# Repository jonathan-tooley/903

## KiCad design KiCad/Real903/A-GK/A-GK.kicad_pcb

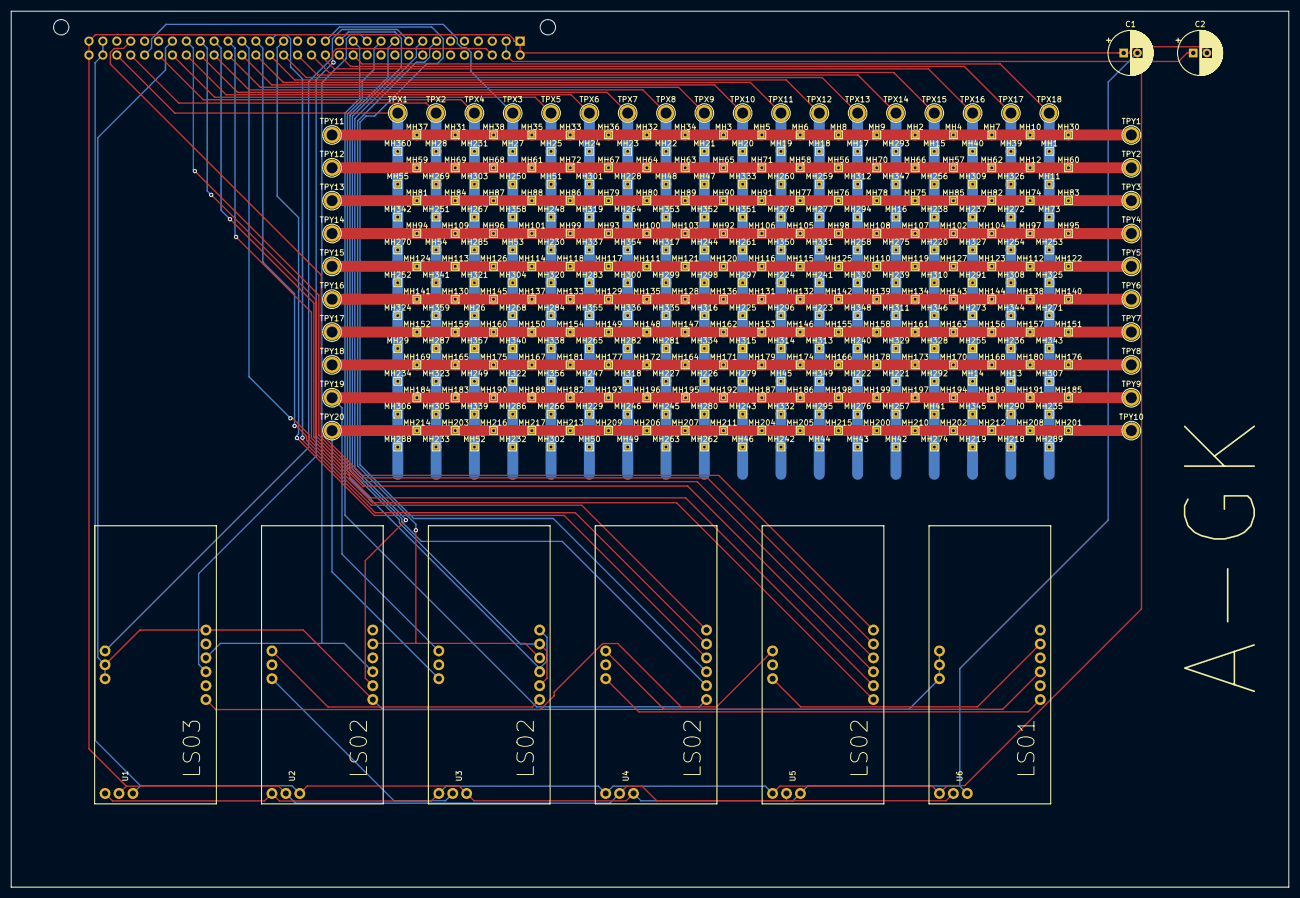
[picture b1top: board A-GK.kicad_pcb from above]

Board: 2 copper layers, 233.3 x 160.0 mm, 407 parts (1 on the bottom side), 57 nets.

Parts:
C1, C2: 6u8; CP_Radial_D8.0mm_P2.50mm
J1: J1; DIN41612_B_2x32_Horizontal
MH1, MH2, MH3, MH4, MH5, MH6, MH7, MH8, MH9, MH10, MH11, MH12, MH13, MH14, MH15, MH16, MH17, MH18, MH19, MH20, MH21, MH22, MH23, MH24, MH25, MH26, MH27, MH28, MH29, MH30, MH31, MH32, MH33, MH34, MH35, MH36, MH37, MH38, MH39, MH40, MH41, MH42, MH43, MH44, MH45, MH46, MH47, MH48, MH49, MH50, MH51, MH52, MH53, MH54, MH55, MH56, MH57, MH58, MH59, MH60, MH61, MH62, MH63, MH64, MH65, MH66, MH67, MH68, MH69, MH70, MH71, MH72, MH73, MH74, MH75, MH76, MH77, MH78, MH79, MH80, MH81, MH82, MH83, MH84, MH85, MH86, MH87, MH88, MH89, MH90, MH91, MH92, MH93, MH94, MH95, MH96, MH97, MH98, MH99, MH100, MH101, MH102, MH103, MH104, MH105, MH106, MH107, MH108, MH109, MH110, MH111, MH112, MH113, MH114, MH115, MH116, MH117, MH118, MH119, MH120, MH121, MH122, MH123, MH124, MH125, MH126, MH127, MH128, MH129, MH130, MH131, MH132, MH133, MH134, MH135, MH136, MH137, MH138, MH139, MH140, MH141, MH142, MH143, MH144, MH145, MH146, MH147, MH148, MH149, MH150, MH151, MH152, MH153, MH154, MH155, MH156, MH157, MH158, MH159, MH160, MH161, MH162, MH163, MH164, MH165, MH166, MH167, MH168, MH169, MH170, MH171, MH172, MH173, MH174, MH175, MH176, MH177, MH178, MH179, MH180, MH181, MH182, MH183, MH184, MH185, MH186, MH187, MH188, MH189, MH190, MH191, MH192, MH193, MH194, MH195, MH196, MH197, MH198, MH199, MH200, MH201, MH202, MH203, MH204, MH205, MH206, MH207, MH208, MH209, MH210, MH211, MH212, MH213, MH214, MH215, MH216, MH217, MH218, MH219, MH220, MH221, MH222, MH223, MH224, MH225, MH226, MH227, MH228, MH229, MH230, MH231, MH232, MH233, MH234, MH235, MH236, MH237, MH238, MH239, MH240, MH241, MH242, MH243, MH244, MH245, MH246, MH247, MH248, MH249, MH250, MH251, MH252, MH253, MH254, MH255, MH256, MH257, MH258, MH259, MH260, MH261, MH262, MH263, MH264, MH265, MH266, MH267, MH268, MH269, MH270, MH271, MH272, MH273, MH274, MH275, MH276, MH277, MH278, MH279, MH280, MH281, MH282, MH283, MH284, MH285, MH286, MH287, MH288, MH289, MH290, MH291, MH292, MH293, MH294, MH295, MH296, MH297, MH298, MH299, MH300, MH301, MH302, MH303, MH304, MH305, MH306, MH307, MH308, MH309, MH310, MH311, MH312, MH313, MH314, MH315, MH316, MH317, MH318, MH319, MH320, MH321, MH322, MH323, MH324, MH325, MH326, MH327, MH328, MH329, MH330, MH331, MH332, MH333, MH334, MH335, MH336, MH337, MH338, MH339, MH340, MH341, MH342, MH343, MH344, MH345, MH346, MH347, MH348, MH349, MH350, MH351, MH352, MH353, MH354, MH355, MH356, MH357, MH358, MH359, MH360: TestPoint_THTPad_1.0x1.0mm_Drill0.5mm
TPX1, TPX2, TPX3, TPX4, TPX5, TPX6, TPX7, TPX8, TPX9, TPX10, TPX11, TPX12, TPX13, TPX14, TPX15, TPX16, TPX17, TPX18: TestPoint_Plated_Hole_D2.0mm
TPY1, TPY2, TPY3, TPY4, TPY5, TPY6, TPY7, TPY8, TPY9, TPY10, TPY11, TPY12, TPY13, TPY14, TPY15, TPY16, TPY17, TPY18, TPY19, TPY20: TestPoint_Plated_Hole_D2.0mm
U1: LS03; LSA
U2, U3, U4, U5: LS02; LSA
U6: LS01; LSA

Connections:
2: MH200.1, MH201.1, MH202.1, MH203.1, MH204.1, MH205.1, MH206.1, MH207.1, MH208.1, MH209.1, MH210.1, MH211.1, MH212.1, MH213.1, MH214.1, MH215.1, MH216.1, MH217.1, TPY10.1, TPY20.1, U3.11
4: MH182.1, MH183.1, MH184.1, MH185.1, MH186.1, MH187.1, MH188.1, MH189.1, MH190.1, MH191.1, MH192.1, MH193.1, MH194.1, MH195.1, MH196.1, MH197.1, MH198.1, MH199.1, TPY9.1, TPY19.1, U3.13
6v: C2.1, J1.2, J1.B, U1.21, U2.21, U3.21, U4.21, U5.21, U6.21
GND: C1.1, C2.2, J1.1, J1.32, J1.A, J1.AL, U1.22, U2.22, U4.22, U5.22, U6.22
II1m: J1.P, MH1.1, MH11.1, MH73.1, MH235.1, MH253.1, MH271.1, MH289.1, MH307.1, MH325.1, MH343.1, TPX18.1
II2m: J1.R, MH13.1, MH39.1, MH218.1, MH236.1, MH254.1, MH272.1, MH290.1, MH308.1, MH326.1, MH344.1, TPX17.1
II3m: J1.S, MH14.1, MH40.1, MH219.1, MH237.1, MH255.1, MH273.1, MH291.1, MH309.1, MH327.1, MH345.1, TPX16.1
II4m: J1.T, MH15.1, MH41.1, MH220.1, MH238.1, MH256.1, MH274.1, MH292.1, MH310.1, MH328.1, MH346.1, TPX15.1
II5m: J1.U, MH16.1, MH42.1, MH221.1, MH239.1, MH257.1, MH275.1, MH293.1, MH311.1, MH329.1, MH347.1, TPX14.1
II6m: J1.V, MH17.1, MH43.1, MH222.1, MH240.1, MH258.1, MH276.1, MH294.1, MH312.1, MH330.1, MH348.1, TPX13.1
II7m: J1.W, MH18.1, MH44.1, MH223.1, MH241.1, MH259.1, MH277.1, MH295.1, MH313.1, MH331.1, MH349.1, TPX12.1
II8m: J1.X, MH19.1, MH45.1, MH224.1, MH242.1, MH260.1, MH278.1, MH296.1, MH314.1, MH332.1, MH350.1, TPX11.1
II9m: J1.Y, MH20.1, MH46.1, MH225.1, MH243.1, MH261.1, MH279.1, MH297.1, MH315.1, MH333.1, MH351.1, TPX10.1
II10m: J1.Z, MH21.1, MH47.1, MH226.1, MH244.1, MH262.1, MH280.1, MH298.1, MH316.1, MH334.1, MH352.1, TPX9.1
II11m: J1.AA, MH22.1, MH48.1, MH227.1, MH245.1, MH263.1, MH281.1, MH299.1, MH317.1, MH335.1, MH353.1, TPX8.1
II12m: J1.AB, MH23.1, MH49.1, MH228.1, MH246.1, MH264.1, MH282.1, MH300.1, MH318.1, MH336.1, MH354.1, TPX7.1
II13m: J1.AC, MH24.1, MH50.1, MH229.1, MH247.1, MH265.1, MH283.1, MH301.1, MH319.1, MH337.1, MH355.1, TPX6.1
II14m: J1.AD, MH25.1, MH51.1, MH230.1, MH248.1, MH266.1, MH284.1, MH302.1, MH320.1, MH338.1, MH356.1, TPX5.1
II15m: J1.AE, MH26.1, MH52.1, MH231.1, MH249.1, MH267.1, MH285.1, MH303.1, MH321.1, MH339.1, MH357.1, TPX4.1
II16m: J1.AF, MH27.1, MH53.1, MH232.1, MH250.1, MH268.1, MH286.1, MH304.1, MH322.1, MH340.1, MH358.1, TPX3.1
II17m: J1.AH, MH28.1, MH54.1, MH233.1, MH251.1, MH269.1, MH287.1, MH305.1, MH323.1, MH341.1, MH359.1, TPX2.1
II18m: J1.AJ, MH29.1, MH55.1, MH234.1, MH252.1, MH270.1, MH288.1, MH306.1, MH324.1, MH342.1, MH360.1, TPX1.1
IIG: J1.26, U1.6, U1.11, U1.12, U2.1, U6.11, U6.12, U6.13
IIG-: J1.9, U1.13
IIS: J1.8, U2.2
J1': J1.7, U2.5, U3.4
J2-': J1.10, U3.2, U3.5
J3': J1.11, U3.3, U3.6
J3-': J1.C, U1.3
J4-: J1.12, U1.4, U2.3
J5: J1.13, U4.1
J6: J1.14, U4.2
J7: J1.15, U4.3
J8: J1.18, U4.4
J9: J1.19, U4.5
J10: J1.20, U4.6
J11: J1.21, U5.1
J12: J1.22, U5.2
J13: J1.23, U5.3
J14-: J1.24, U5.4
J15-: J1.25, U5.5
J16-: J1.29, U5.6
Neg6v: C1.2, J1.31, J1.AK, U1.23, U2.23, U3.23, U4.23, U5.23, U6.23
unnamed: MH2.1, MH3.1, MH4.1, MH5.1, MH6.1, MH7.1, MH8.1, MH9.1, MH10.1, MH30.1, MH31.1, MH32.1, MH33.1, MH34.1, MH35.1, MH36.1, MH37.1, MH38.1, TPY1.1, TPY11.1
unnamed: MH12.1, MH56.1, MH57.1, MH58.1, MH59.1, MH60.1, MH61.1, MH62.1, MH63.1, MH64.1, MH65.1, MH66.1, MH67.1, MH68.1, MH69.1, MH70.1, MH71.1, MH72.1, TPY2.1, TPY12.1
unnamed: MH74.1, MH75.1, MH76.1, MH77.1, MH78.1, MH79.1, MH80.1, MH81.1, MH82.1, MH83.1, MH84.1, MH85.1, MH86.1, MH87.1, MH88.1, MH89.1, MH90.1, MH91.1, TPY3.1, TPY13.1
unnamed: MH92.1, MH93.1, MH94.1, MH95.1, MH96.1, MH97.1, MH98.1, MH99.1, MH100.1, MH101.1, MH102.1, MH103.1, MH104.1, MH105.1, MH106.1, MH107.1, MH108.1, MH109.1, TPY4.1, TPY14.1
unnamed: MH110.1, MH111.1, MH112.1, MH113.1, MH114.1, MH115.1, MH116.1, MH117.1, MH118.1, MH119.1, MH120.1, MH121.1, MH122.1, MH123.1, MH124.1, MH125.1, MH126.1, MH127.1, TPY5.1, TPY15.1
unnamed: MH128.1, MH129.1, MH130.1, MH131.1, MH132.1, MH133.1, MH134.1, MH135.1, MH136.1, MH137.1, MH138.1, MH139.1, MH140.1, MH141.1, MH142.1, MH143.1, MH144.1, MH145.1, TPY6.1, TPY16.1
unnamed: MH146.1, MH147.1, MH148.1, MH149.1, MH150.1, MH151.1, MH152.1, MH153.1, MH154.1, MH155.1, MH156.1, MH157.1, MH158.1, MH159.1, MH160.1, MH161.1, MH162.1, MH163.1, TPY7.1, TPY17.1
unnamed: MH164.1, MH165.1, MH166.1, MH167.1, MH168.1, MH169.1, MH170.1, MH171.1, MH172.1, MH173.1, MH174.1, MH175.1, MH176.1, MH177.1, MH178.1, MH179.1, MH180.1, MH181.1, TPY8.1, TPY18.1
unnamed: U1.1, U5.13
unnamed: U2.13, U3.1
unnamed: U4.11, U6.1
unnamed: U4.13, U6.3
unnamed: U5.11, U6.5
U3GND: U2.11, U3.22

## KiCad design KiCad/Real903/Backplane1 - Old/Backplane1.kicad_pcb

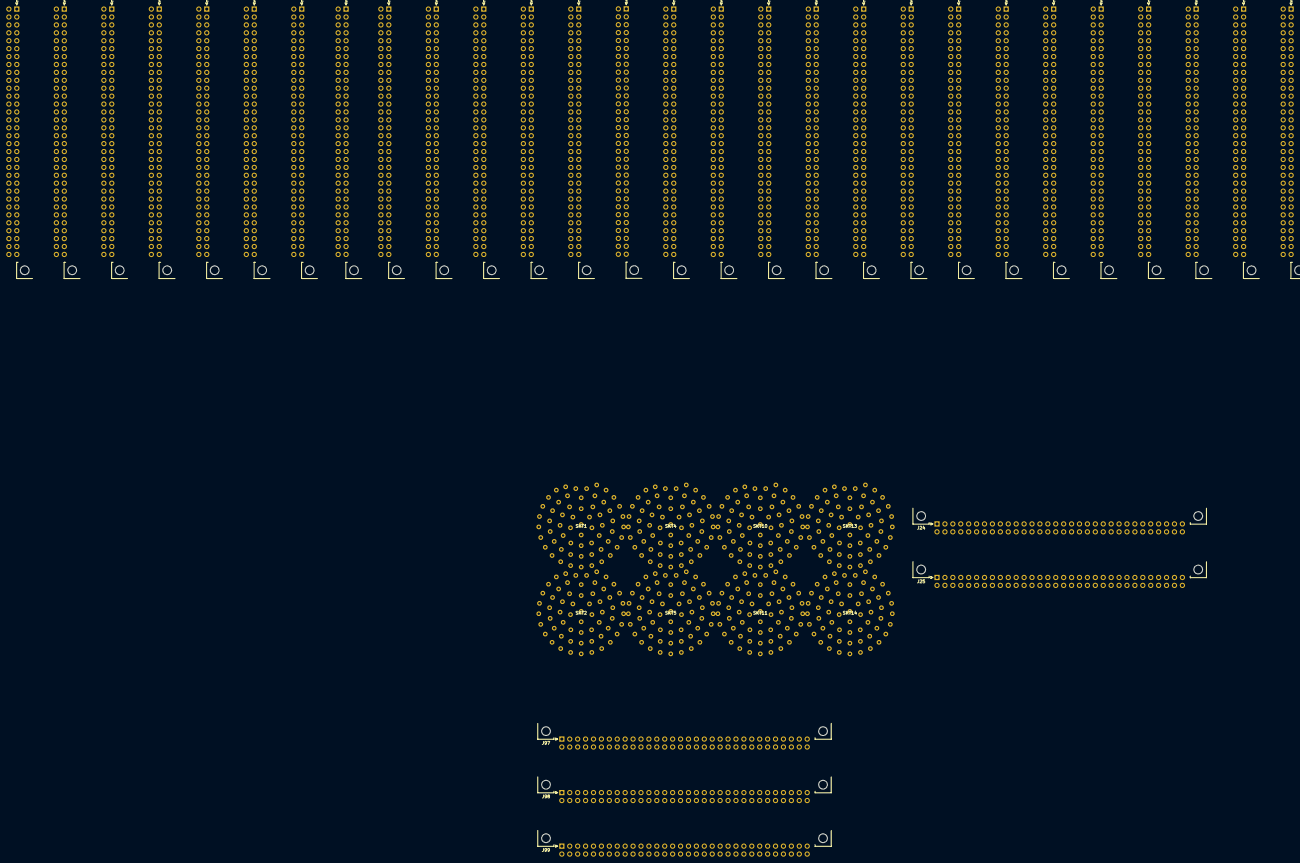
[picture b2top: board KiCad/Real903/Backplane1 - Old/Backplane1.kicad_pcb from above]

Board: 8 copper layers, 41 parts (0 on the bottom side), 564 nets, no tracks yet.

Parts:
J24, J25, J28, J29, J30, J31, J32, J34, J35, J36, J37, J38, J39, J40, J41, J42, J43, J44, J45, J46, J47, J48, J49, J50, J51, J52, J53, J54, J55, J56, J97, J98, J99: Conn_02x32; DIN41612_B_2x32_Horizontal
SKT1, SKT2, SKT4, SKT5, SKT10, SKT11, SKT13, SKT14: SKT61; MC61

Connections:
0TM1-: J46.15, J48.20, J49.20, J50.20, J51.20, J52.20, J53.20, J54.20, J55.20
0TM2-: J37.20, J38.20, J39.20, J40.20, J41.20, J42.20, J43.20, J44.20, J45.20, J46.16, J56.20
6V: J24.B, J25.B
6v: J24.2, J25.2, J28.2, J28.B, J29.2, J29.B, J30.2, J30.B, J31.2, J31.B, J32.2, J32.B, J34.2, J34.B, J35.2, J35.B, J36.2, J36.B, J37.2, J37.B, J38.2, J38.B, J39.2, J39.B, J40.2, J40.B, J41.2, J41.B, J42.2, J42.B, J43.2, J43.B, J44.2, J44.B, J45.2, J45.B, J46.2, J46.B, J47.2, J47.B, J48.2, J48.B, J49.2, J49.B, J50.2, J50.B, J51.2, J51.B, J52.2, J52.B, J53.2, J53.B, J54.2, J54.B, J55.2, J55.B, J56.2, J56.B, J99.2, J99.B
/RegistersA/C10: J44.C, J45.3
/RegistersA/C11: J43.C, J44.3
/RegistersA/C12: J42.C, J43.3
/RegistersA/C13: J41.C, J42.3
/RegistersA/C14: J40.C, J41.3
/RegistersA/C15: J39.C, J40.3
/RegistersA/C16: J38.C, J39.3
/RegistersB/C1: J55.C, J56.3
/RegistersB/C2: J54.C, J55.3
/RegistersB/C3: J53.C, J54.3
/RegistersB/C4: J52.C, J53.3
/RegistersB/C5: J51.C, J52.3
/RegistersB/C6: J50.C, J51.3
/RegistersB/C7: J49.C, J50.3
/RegistersB/C8: J48.C, J49.3
A1-: J29.AJ, J31.C, J31.Y, J56.AB
A2: J48.12, J55.27
A2-: J31.D, J31.Z, J55.AB
A3: J45.12, J54.27
A3-: J31.AA, J31.E, J54.AB
A4: J44.12, J53.27
A4-: J31.AB, J31.F, J53.AB
A5: J43.12, J52.27
A5-: J31.AC, J31.H, J52.AB
A6: J42.12, J51.27
A6-: J31.AD, J31.J, J51.AB
A7: J41.12, J50.27
A7-: J31.AE, J31.K, J50.AB
A8: J40.12, J49.27
A8-: J31.AF, J31.L, J49.AB
A9: J39.12, J48.27
A9-: J31.M, J48.AB
A10: J38.12, J45.27
A10-: J31.N, J45.AB
A11: J37.12, J44.27
A11-: J31.P, J44.AB
A12-: J31.R, J43.AB
A13-: J31.S, J42.AB
A14-: J31.T, J41.AB
A15-: J31.U, J40.AB
A16-: J31.V, J39.AB
A17-: J31.W, J38.AB
A18-: J31.X, J37.AB
ATF1: J47.27, J48.28, J49.28, J50.28, J51.28, J52.28, J53.28, J54.28, J55.28, J56.28
ATF2: J37.28, J38.28, J39.28, J40.28, J41.28, J42.28, J43.28, J44.28, J45.28, J47.28
ATFa: J47.AC, J99.AH
C9: J45.C, J48.3
C17: J37.C, J38.3, J98.6
C18: J37.3, J98.5
CRS: J46.5, J99.10
CRSm: J46.E, J99.12
DTF1-1: J50.29, J51.29, J52.29, J53.29, J54.29, J55.29, J56.29
DTF1-2: J42.29, J43.29, J44.29, J45.29, J48.29, J49.29
DTF2a: J37.29, J38.29, J39.29, J40.29, J41.29
ETJ2-: J55.N, J98.10
ETJ3-: J54.N, J98.11
F1: J55.D, J56.E, J98.3
F2: J54.D, J55.E, J56.5
F3: J53.D, J54.E, J55.5
F4: J52.D, J53.E, J54.5
F5: J51.D, J52.E, J53.5
F6: J50.D, J51.E, J52.5
F7: J49.D, J50.E, J51.5
F8: J48.D, J49.E, J50.5
F9: J45.D, J48.E, J49.5
F10: J44.D, J45.E, J48.5
F11: J43.D, J44.E, J45.5
F12: J42.D, J43.E, J44.5
F13: J41.D, J42.E, J43.5
F14: J40.D, J41.E, J42.5
F15: J39.D, J40.E, J41.5
F16: J38.D, J39.E, J40.5
F17: J37.D, J38.E, J39.5
F18: J37.E, J38.5, J98.4
FTG1: J47.4, J48.6, J49.6, J50.6, J51.6, J52.6, J53.6, J54.6, J55.6, J56.6
FTG2: J37.6, J38.6, J39.6, J40.6, J41.6, J42.6, J43.6, J44.6, J45.6, J47.3
FTGa: J47.C, J99.AF
GND: J24.1, J24.32, J24.A, J24.AL, J25.1, J25.32, J25.A, J25.AL, J28.1, J28.32, J28.A, J28.AL, J29.1, J29.32, J29.A, J29.AL, J30.1, J30.32, J30.A, J30.AL, J31.1, J31.32, J31.A, J31.AL, J32.1, J32.32, J32.A, J32.AL, J34.1, J34.32, J34.A, J34.AL, J35.1, J35.32, J35.A, J35.AL, J36.1, J36.32, J36.A, J36.AL, J37.1, J37.32, J37.A, J37.AL, J38.1, J38.32, J38.A, J38.AL, J39.1, J39.32, J39.A, J39.AL, J40.1, J40.32, J40.A, J40.AL, J41.1, J41.32, J41.A, J41.AL, J42.1, J42.32, J42.A, J42.AL, J43.1, J43.32, J43.A, J43.AL, J44.1, J44.32, J44.A, J44.AL, J45.1, J45.32, J45.A, J45.AL, J46.1, J46.32, J46.A, J46.AL, J47.1, J47.32, J47.A, J47.AL, J48.1, J48.32, J48.A, J48.AL, J49.1, J49.32, J49.A, J49.AL, J50.1, J50.32, J50.A, J50.AL, J51.1, J51.32, J51.A, J51.AL, J52.1, J52.32, J52.A, J52.AL, J53.1, J53.32, J53.A, J53.AL, J54.1, J54.32, J54.A, J54.AL, J55.1, J55.32, J55.A, J55.AL, J56.1, J56.32, J56.A, J56.AL, J99.1, J99.32, J99.A, J99.AL, SKT2.MM
GTA1: J46.23, J48.23, J49.23, J50.23, J51.23, J52.23, J53.23, J54.23, J55.23, J56.23
GTA2: J37.23, J38.23, J39.23, J40.23, J41.23, J42.23, J43.23, J44.23, J45.23, J46.24
GTAa: J46.AA, J99.D
GTJ1: J46.13, J48.13, J49.13, J50.13, J51.13, J52.13, J53.13, J54.13, J55.13, J56.13
GTJ2: J37.13, J38.13, J39.13, J40.13, J41.13, J42.13, J43.13, J44.13, J45.13, J46.14
GTJa: J46.P, J99.22
GTM1: J46.19, J48.17, J49.17, J50.17, J51.17, J52.17, J53.17, J54.17, J55.17, J56.17
GTM2: J37.17, J38.17, J39.17, J40.17, J41.17, J42.17, J43.17, J44.17, J45.17, J46.20
GTMa: J46.W, J99.14
GTQ1: J46.27, J48.AE, J49.AE, J50.AE, J51.AE, J52.AE, J53.AE, J54.AE, J55.AE, J56.AE
GTQ2: J37.AE, J38.AE, J39.AE, J40.AE, J41.AE, J42.AE, J43.AE, J44.AE, J45.AE, J46.28
GTQa: J46.AC, J99.13
I1: J41.21, J98.J
I1-: J41.W, J98.D
I2: J40.21, J98.H
I2-: J40.W, J98.C
I3: J39.21, J98.F
I3-: J39.W, J98.B
I4: J38.21, J98.E
I4-: J38.W, J98.A
II1: J34.13, J56.25
II1m: J34.P, J35.P, J36.P
II2: J34.14, J55.25
II2m: J34.R, J35.R, J36.R
II3: J34.15, J54.25
II3m: J34.S, J35.S, J36.S
II4: J34.16, J53.25
II4m: J34.T, J35.T, J36.T
II5: J34.17, J52.25
II5m: J34.U, J35.U, J36.U
II6: J34.18, J51.25
II6m: J34.V, J35.V, J36.V
II7: J34.19, J50.25
II7m: J34.W, J35.W, J36.W
II8: J34.20, J49.25
II8m: J34.X, J35.X, J36.X
II9: J34.21, J48.25
II9m: J34.Y, J35.Y, J36.Y
II10: J34.22, J45.25
II10m: J34.Z, J35.Z, J36.Z
II11: J34.23, J44.25
II11m: J34.AA, J35.AA, J36.AA
II12: J34.24, J43.25
II12m: J34.AB, J35.AB, J36.AB
II13: J34.25, J42.25
II13m: J34.AC, J35.AC, J36.AC
II14: J34.26, J41.25
II14m: J34.AD, J35.AD, J36.AD
II15: J34.27, J40.25
II15m: J34.AE, J35.AE, J36.AE
II16: J34.28, J39.25
II16m: J34.AF, J35.AF, J36.AF
II17: J34.12, J38.25
II17m: J34.N, J35.AH, J36.AH
II18: J34.30, J37.25
II18m: J34.AJ, J35.AJ, J36.AJ
IIG: J35.26, J36.26
IIS: J35.15, J36.8, J99.X
INT1: J29.27, J98.AJ
INT2: J29.28, J98.AH
INT3: J29.29, J98.AF
IP1: J28.3, J56.9
IP2: J28.4, J55.9
IP3: J28.5, J54.9
IP4: J28.6, J53.9
IP5: J28.7, J52.9
IP6: J28.8, J51.9
IP7: J28.9, J50.9
IP8: J28.10, J49.9
IP9: J28.11, J48.9
IP10: J28.14, J45.9
IP11: J28.15, J44.9
IP12: J28.16, J43.9
IP13: J28.17, J42.9
IP14: J28.18, J41.9
IP15: J28.19, J40.9
IP16: J28.24, J39.9
IP17: J28.25, J38.9
IP18: J28.26, J37.9
IP'1: J29.3, J56.12
IP'2: J29.4, J55.12
IP'3: J29.5, J54.12
IP'4: J29.6, J53.12
IP'5: J29.10, J52.12
IP'6: J29.7, J51.12
IP'7: J29.8, J50.12
IP'8: J29.9, J49.12
ITF: J56.C, J98.K
J1': J35.7, J36.7, J98.13
J1-: J56.R, J97.13
J1-': J35.8, J98.12
J2': J35.9, J98.15
J2-: J55.R, J97.12
J2-': J35.10, J36.10, J98.14
J3': J35.11, J36.11, J98.17
J3-: J54.R, J97.11
J3-': J35.12, J36.C, J98.16
J4: J35.14, J53.T
J4-: J35.13, J36.12, J53.R, J97.10
J5: J36.13, J52.T
J5-: J24.3, J52.R, J97.9
J6: J36.14, J51.T
J6-: J24.8, J51.R, J97.8
J7: J36.15, J50.T
J7-: J24.19, J50.R, J97.7
J8: J36.18, J49.T
J8-: J24.27, J49.R, J97.6
J9: J36.19, J48.T
J9-: J25.3, J48.R, J97.5
J10: J36.20, J45.T
J10-: J25.8, J45.R, J97.4
J11: J36.21, J44.T
J11-: J25.19, J44.R, J97.3
J12: J36.22, J43.T
J12-: J25.27, J43.R, J97.2
J13: J36.23, J42.T
J13-: J42.R, J97.1
J14: J41.T, J47.Z
J14-: J36.24, J41.R, J99.26
J15: J40.T, J47.29
J15-: J36.25, J40.R, J99.27
J16: J39.T, J47.V
J16-: J36.29, J39.R, J99.28
JTF1: J47.15, J48.14, J49.14, J50.14, J51.14, J52.14, J53.14, J54.14, J55.14, J56.14
JTF2: J37.14, J38.14, J39.14, J40.14, J41.14, J42.14, J43.14, J44.14, J45.14, J47.16
JTFa: J47.S, J99.7
JTG14-: J41.4, J47.AE
JTG15-: J40.4, J47.AH
JTG16-: J39.4, J47.T
JTPC: J24.L, J25.L, J47.23, J47.24, J99.8
JTPCa: J47.AA, J99.Z
KTJ1-: J56.N, J98.9
KTJ5-: J52.N, J98.8
LTG1: J47.7, J48.H, J49.H, J50.H, J51.H, J52.H, J53.H, J54.H, J55.H, J56.H
LTG2: J37.H, J38.H, J39.H, J40.H, J41.H, J42.H, J43.H, J44.H, J45.H, J47.8
LTGa: J47.H, J99.AE
M1-: J56.V, J97.V
M2-: J55.V, J97.U
M3-: J54.V, J97.T
M4-: J53.V, J97.S
M5-: J52.V, J97.R
M6-: J51.V, J97.P
M7-: J50.V, J97.N
M8-: J49.V, J97.M
M9-: J48.V, J97.L
M10-: J45.V, J97.K
M11: J44.AD, J98.AB
M11-: J44.V, J97.J
M12: J43.AD, J98.AC
M12-: J43.V, J97.H
M13: J42.AD, J98.AD
M13-: J42.V, J97.F
M14-: J41.V, J97.E
M15-: J40.V, J97.D
M16-: J39.V, J97.C
M17-: J38.V, J97.B
M18: J37.AD, J98.AE
M18-: J37.V, J97.A
M-TF1: J47.19, J48.16, J49.16, J50.16, J51.16, J52.16, J53.16, J54.16, J55.16, J56.16
M-TF2: J37.16, J38.16, J39.16, J40.16, J41.16, J42.16, J43.16, J44.16, J45.16, J47.20
M-TFa: J47.W, J99.5
MTF1: J47.17, J48.15, J49.15, J50.15, J51.15, J52.15, J53.15, J54.15, J55.15, J56.15
MTF2: J37.15, J38.15, J39.15, J40.15, J41.15, J42.15, J43.15, J44.15, J45.15, J47.18
MTFa: J47.U, J99.6
MTI: J38.22, J39.22, J40.22, J41.22, J47.X, J98.7
MTP1: J47.21, J48.22, J49.22, J50.22, J51.22, J52.22, J53.22, J54.22, J55.22, J56.22
MTP2: J42.22, J43.22, J44.22, J45.22, J47.22
MTPa: J46.Y, J47.Y, J99.17
Neg6v: J24.31, J24.AK, J25.31, J25.AK, J28.31, J28.AK, J29.31, J29.AK, J30.31, J30.AK, J31.31, J31.AK, J32.31, J32.AK, J34.31, J34.AK, J35.31, J35.AK, J36.31, J36.AK, J37.31, J37.AK, J38.31, J38.AK, J39.31, J39.AK, J40.31, J40.AK, J41.31, J41.AK, J42.31, J42.AK, J43.31, J43.AK, J44.31, J44.AK, J45.31, J45.AK, J46.31, J46.AK, J47.31, J47.AK, J48.31, J48.AK, J49.31, J49.AK, J50.31, J50.AK, J51.31, J51.AK, J52.31, J52.AK, J53.31, J53.AK, J54.31, J54.AK, J55.31, J55.AK, J56.31, J56.AK, J99.31, J99.AK
unnamed: J24.28, J25.5
OTA1-: J46.25, J48.AA, J49.AA, J50.AA, J51.AA, J52.AA, J53.AA, J54.AA, J55.AA, J56.AA
OTA2-: J37.AA, J38.AA, J39.AA, J40.AA, J41.AA, J42.AA, J43.AA, J44.AA, J45.AA, J46.26
OTA-': J46.Z, J99.C
OTG1-: J46.9, J46.29, J48.10, J49.10, J50.10, J51.10, J52.10, J53.10, J54.10, J55.10, J56.10
OTG2-: J37.10, J38.10, J39.10, J40.10, J41.10, J42.10, J43.10, J44.10, J45.10, J46.10, J46.AB
OTI-: J38.X, J39.X, J40.X, J41.X
OTJ1-: J46.11, J48.P, J49.P, J50.P, J51.P, J52.P, J53.P, J54.P, J55.P, J56.P
OTJ2-: J37.P, J38.P, J39.P, J40.P, J41.P, J42.P, J43.P, J44.P, J45.P, J46.12
OTJ-: J46.M, J99.23
OTMa: J46.S, J99.20
OTP1-: J46.21, J50.X, J51.X, J52.X, J53.X, J54.X, J55.X, J56.X
OTP2-: J42.X, J43.X, J44.X, J45.X, J46.22, J48.X, J49.X
OTQ1-: J48.26, J49.26, J50.26, J51.26, J52.26, J53.26, J54.26, J55.26, J56.26
OTQ2-: J37.26, J38.26, J39.26, J40.26, J41.26, J42.26, J43.26, J44.26, J45.26
P1-: J32.C, J32.U, J56.W
P2-: J32.D, J32.S, J55.W
P3-: J32.E, J32.V, J54.W
P4-: J32.F, J32.W, J53.W
P5-: J30.AC, J32.H, J52.W
P6-: J30.24, J32.J, J51.W
P7-: J30.AA, J32.K, J50.W
P8-: J30.22, J32.L, J49.W
P9-: J30.Y, J32.M, J48.W
P10-: J30.X, J32.N, J45.W
P11-: J30.W, J32.P, J44.W
P12: J30.V, J43.21
P12-: J30.T, J43.W
P13: J30.13, J42.21
P13-: J30.18, J42.W
PC5-12: J24.20, J25.20
PTG1-1: J47.10, J48.L, J49.L, J50.L, J51.L, J52.L, J53.L, J54.L, J55.L, J56.L
PTG1-2: J37.L, J38.L, J39.L, J40.L, J41.L, J42.L, J43.L, J44.L, J45.L, J47.9
PTG1-a: J47.K, J99.AB
PTG2-1: J47.11, J48.11, J49.11, J50.11, J51.11, J52.11, J53.11, J54.11, J55.11, J56.11
PTG2-2: J37.11, J38.11, J39.11, J40.11, J41.11, J42.11, J43.11, J44.11, J45.11, J47.12
PTG2-a: J47.M, J99.AA
PulseGen: J24.12, J25.12
QTF1: J47.25, J48.30, J49.30, J50.30, J51.30, J52.30, J53.30, J54.30, J55.30, J56.30
QTF2: J37.30, J38.30, J39.30, J40.30, J41.30, J42.30, J43.30, J44.30, J45.30, J47.26
QTFa: J47.AB, J99.3, J99.AJ
RBT: J28.27, J98.32
RBTm: J28.AE, J98.30
RESET2-: J32.T, J32.X, J46.AH, J99.25
RGS-x: J29.21, J98.AL
RTG1: J47.6, J48.7, J49.7, J50.7, J51.7, J52.7, J53.7, J54.7, J55.7, J56.7
RTG2: J37.7, J38.7, J39.7, J40.7, J41.7, J42.7, J43.7, J44.7, J45.7, J47.5
RTGa: J47.E, J99.AD
SBT: J28.29, J98.31
SBTm: J28.AH, J98.29
SFD: J46.6, J99.9
SFDm: J46.F, J99.11
SKT1AA: J44.AC, SKT1.AA
SKT1B: J56.M, SKT1.B
SKT1BB: J43.AC, SKT1.BB
SKT1C: J55.M, SKT1.C
SKT1CC: J42.AC, SKT1.CC
SKT1D: J54.M, SKT1.D
SKT1DD: J41.AC, SKT1.DD
SKT1E: J53.M, SKT1.E
SKT1EE: J40.AC, SKT1.EE
SKT1F: J52.M, SKT1.F
SKT1FF: J39.AC, SKT1.FF
SKT1G: J51.M, SKT1.G
SKT1GG: J38.AC, SKT1.GG
SKT1H: J50.M, SKT1.H
SKT1HH: J37.AC, SKT1.HH
SKT1J: J49.M, SKT1.J
SKT1K: J48.M, SKT1.K
SKT1L: J45.M, SKT1.L
SKT1LL: J30.P, SKT1.LL
SKT1M: J44.M, SKT1.M
SKT1MM: J30.Z, SKT1.MM
SKT1N: J43.M, SKT1.N
SKT1P: J42.M, SKT1.P
SKT1PP: J30.H, SKT1.PP
SKT1R: J41.M, SKT1.R
SKT1S: J40.M, SKT1.S
SKT1T: J39.M, SKT1.T
SKT1U: J38.M, SKT1.U
SKT1V: J37.M, SKT1.V
SKT1W: J56.Z, SKT1.W
SKT1X: J55.Z, SKT1.X
SKT1Y: J54.Z, SKT1.Y
SKT1Z: J53.Z, SKT1.Z
SKT1a: J52.Z, SKT1.a
SKT1b: J51.Z, SKT1.b
SKT1c: J50.Z, SKT1.c
SKT1d: J49.Z, SKT1.d
SKT1e: J48.Z, SKT1.e
SKT1f: J45.Z, SKT1.f
SKT1g: J44.Z, SKT1.g
SKT1h: J43.Z, SKT1.h
SKT1i: J42.Z, SKT1.i
SKT1j: J41.Z, SKT1.j
SKT1k: J40.Z, SKT1.k
SKT1m: J39.Z, SKT1.m
SKT1n: J38.Z, SKT1.n
SKT1p: J37.Z, SKT1.p
SKT1q: J56.AC, SKT1.q
SKT1r: J55.AC, SKT1.r
SKT1s: J54.AC, SKT1.s
SKT1t: J53.AC, SKT1.t
SKT1u: J52.AC, SKT1.u
SKT1v: J51.AC, SKT1.v
SKT1w: J50.AC, SKT1.w
SKT1x: J49.AC, SKT1.x
SKT1y: J48.AC, SKT1.y
SKT1z: J45.AC, SKT1.z
SKT2B: J56.U, SKT2.B
SKT2C: J55.U, SKT2.C
SKT2D: J54.U, SKT2.D
SKT2DD: J24.P, SKT2.DD
SKT2E: J53.U, SKT2.E
SKT2EE: J24.K, SKT2.EE
SKT2F: J52.U, SKT2.F
SKT2FF: J24.V, SKT2.FF
SKT2G: J51.U, SKT2.G
SKT2GG: J24.Y, SKT2.GG
SKT2H: J50.U, SKT2.H
SKT2HH: J25.P, SKT2.HH
SKT2J: J49.U, SKT2.J
SKT2JJ: J25.K, SKT2.JJ
SKT2K: J48.U, SKT2.K
SKT2KK: J25.V, SKT2.KK
SKT2L: J45.U, SKT2.L
SKT2LL: J25.Y, SKT2.LL
SKT2M: J44.U, SKT2.M
SKT2N: J43.U, SKT2.N
SKT2P: J42.U, SKT2.P
SKT2R: J41.U, SKT2.R
SKT2S: J40.U, SKT2.S
SKT2T: J39.U, SKT2.T
SKT2U: J38.U, SKT2.U
SKT2V: J37.U, SKT2.V
SKT2W: J56.S, SKT2.W
SKT2X: J55.S, SKT2.X
SKT2Y: J54.S, SKT2.Y
SKT2Z: J53.S, SKT2.Z
SKT2a: J52.S, SKT2.a
SKT2b: J51.S, SKT2.b
SKT2c: J50.S, SKT2.c
SKT2d: J49.S, SKT2.d
SKT2e: J48.S, SKT2.e
SKT2f: J45.S, SKT2.f
SKT2g: J44.S, SKT2.g
SKT2h: J43.S, SKT2.h
SKT2i: J42.S, SKT2.i
SKT2j: J41.S, SKT2.j
SKT2k: J40.S, SKT2.k
SKT2m: J39.S, SKT2.m
SKT2n: J56.Y, SKT2.n
SKT2p: J55.Y, SKT2.p
SKT2q: J54.Y, SKT2.q
SKT2r: J53.Y, SKT2.r
SKT2s: J52.Y, SKT2.s
SKT2t: J51.Y, SKT2.t
SKT2u: J50.Y, SKT2.u
SKT2v: J49.Y, SKT2.v
SKT2w: J48.Y, SKT2.w
SKT2x: J45.Y, SKT2.x
SKT2y: J44.Y, SKT2.y
SKT3r: J41.Y, J98.AA
SKT3s: J40.Y, J98.Z
SKT3t: J39.Y, J98.Y
SKT3u: J38.Y, J98.X
SKT4AA: J28.S, SKT14.AA
SKT4B: J31.3, SKT4.B
SKT4BB: J28.T, SKT14.BB
SKT4C: J31.4, SKT4.C
SKT4CC: J28.U, SKT14.CC
SKT4D: J31.5, SKT4.D
SKT4DD: J28.V, SKT14.DD
SKT4E: J31.6, SKT4.E
SKT4EE: J28.W, SKT14.EE
SKT4F: J31.7, SKT4.F
SKT4FF: J28.AB, SKT14.FF
SKT4G: J31.8, SKT4.G
SKT4GG: J28.AC, SKT14.GG
SKT4H: J31.9, SKT4.H
SKT4HH: J28.AD, SKT14.HH
SKT4J: J31.10, SKT4.J
SKT4K: J31.11, SKT4.K
SKT4L: J31.12, SKT4.L
SKT4M: J31.13, SKT4.M
SKT4N: J31.14, SKT4.N
SKT4P: J31.15, SKT4.P
SKT4PP: J32.20, SKT4.NN
SKT4R: J31.16, SKT4.R
SKT4S: J31.17, SKT4.S
SKT4T: J31.18, SKT4.T
SKT4U: J31.19, SKT4.U
SKT4V: J31.20, SKT4.V
SKT4W: J32.3, SKT4.W
SKT4X: J32.4, SKT4.X
SKT4Y: J32.5, SKT4.Y
SKT4Z: J32.6, SKT4.Z
SKT4a: J32.7, SKT4.a
SKT4b: J32.8, SKT4.b
SKT4c: J32.9, SKT4.c
SKT4d: J32.10, SKT4.d
SKT4e: J32.11, SKT4.e
SKT4f: J32.12, SKT4.f
SKT4g: J32.13, SKT4.g
SKT4q: J28.C, SKT4.q
SKT4r: J28.D, SKT4.r
SKT4s: J28.E, SKT4.s
SKT4t: J28.F, SKT4.t
SKT4u: J28.H, SKT4.u
SKT4v: J28.J, SKT4.v
SKT4w: J28.K, SKT4.w
SKT4x: J28.L, SKT4.x
SKT4y: J28.M, SKT4.y
SKT4z: J28.R, SKT4.z
SKT5p: J32.14, SKT5.p
SKT10A: J29.C, SKT10.A
SKT10B: J29.D, SKT10.B
SKT10C: J29.E, SKT10.C
SKT10D: J29.F, SKT10.D
SKT10E: J29.L, SKT10.E
SKT10F: J29.H, SKT10.F
SKT10G: J29.J, SKT10.G
SKT10H: J29.K, SKT10.H
SKT10J: J31.21, SKT10.J
SKT10K: J31.22, SKT10.K
SKT10L: J31.23, SKT10.L
SKT10M: J31.24, SKT10.M
SKT10N: J31.25, SKT10.N
SKT10P: J31.26, SKT10.P
SKT10R: J31.27, SKT10.R
SKT10S: J31.28, SKT10.S
SKT10U: J32.18, SKT10.U
SKT10V: J30.14, SKT10.V
SKT10W: J30.D, SKT10.W
SKT10X: J32.17, SKT10.X
SKT10Y: J32.15, SKT10.Y
SKT10b: J32.19, SKT10.b
SKT10d: J32.16, SKT10.d
SKT10h: J30.15, SKT10.h
SKT10j: J30.C, SKT10.j
SKT11B: J56.18, SKT11.B
SKT11C: J29.U, SKT11.C
SKT11D: J29.T, SKT11.D
SKT11E: J29.S, SKT11.E
SKT11F: J52.18, SKT11.F
SKT11G: J51.18, SKT11.G
SKT11H: J50.18, SKT11.H
SKT11J: J49.18, SKT11.J
SKT11K: J48.18, SKT11.K
SKT11L: J45.18, SKT11.L
SKT11M: J44.18, SKT11.M
SKT11N: J43.18, SKT11.N
SKT11P: J42.18, SKT11.P
SKT11R: J29.P, SKT11.R
SKT11S: J29.V, SKT11.S
SKT11T: J29.N, SKT11.T
SKT11V: J29.R, SKT11.V
SKT13A: J29.AE, SKT13.A
SKT13C: J29.AF, SKT13.C
SKT13E: J29.AH, SKT13.E
SKT13G: J30.20, SKT13.G
SKT13J: J30.21, SKT13.J
SKT13L: J30.E, SKT13.L
SKT13N: J30.U, SKT13.N
SKT13R: J30.12, SKT13.R
SKT14x: J29.AA, SKT14.x
SKT14z: J29.Z, SKT14.z
STORE1-: J56.AJ, J97.14
STORE2-: J55.AJ, J97.15
STORE3-: J54.AJ, J97.16
STORE4-: J53.AJ, J97.17
STORE5-: J52.AJ, J97.18
STORE6-: J51.AJ, J97.19
STORE7-: J50.AJ, J97.20
STORE8-: J49.AJ, J97.21
STORE9-: J48.AJ, J97.22
STORE10-: J45.AJ, J97.23
STORE11-: J44.AJ, J97.24
STORE12-: J43.AJ, J97.25
STORE13-: J42.AJ, J97.26
STORE14-: J41.AJ, J97.27
STORE15-: J40.AJ, J97.28
STORE16-: J39.AJ, J97.29
STORE17-: J38.AJ, J97.30
STORE18-: J37.AJ, J97.31
SZ1: J30.J, J98.26
TZ1: J30.F, J98.27
VTG1: J47.14, J48.8, J49.8, J50.8, J51.8, J52.8, J53.8, J54.8, J55.8, J56.8
VTG2: J37.8, J38.8, J39.8, J40.8, J41.8, J42.8, J43.8, J44.8, J45.8, J47.13
VTG-: J32.R, J47.R
VTGa: J47.P, J99.AC
W2: J29.15, J55.18
W3: J29.16, J54.18
W4: J29.17, J53.18
W14: J29.13, J41.18
W15: J29.20, J40.18
W16: J29.12, J39.18
W17: J38.18, J99.F
W18: J29.14, J37.18
WFR: J24.14, J25.14
WGS-x: J29.23, J98.AK
WTM1: J46.17, J48.19, J49.19, J50.19, J51.19, J52.19, J53.19, J54.19, J55.19, J56.19
WTM2: J37.19, J38.19, J39.19, J40.19, J41.19, J42.19, J43.19, J44.19, J45.19, J46.18
WTMa: J46.U, J99.19
X0: J56.D, J98.1
X1: J37.5, J98.2
Z2-: J30.28, J98.25
t1: J46.AF, J98.L
t2-2: J47.AF, J98.M
t3-2: J46.AE, J98.N
t4: J46.AD, J98.P
t4-2: J30.M, J98.R
t5: J47.AD, J98.S
